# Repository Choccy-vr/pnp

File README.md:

# pnp
A manual precise pick and place machine for parts as small as 0402

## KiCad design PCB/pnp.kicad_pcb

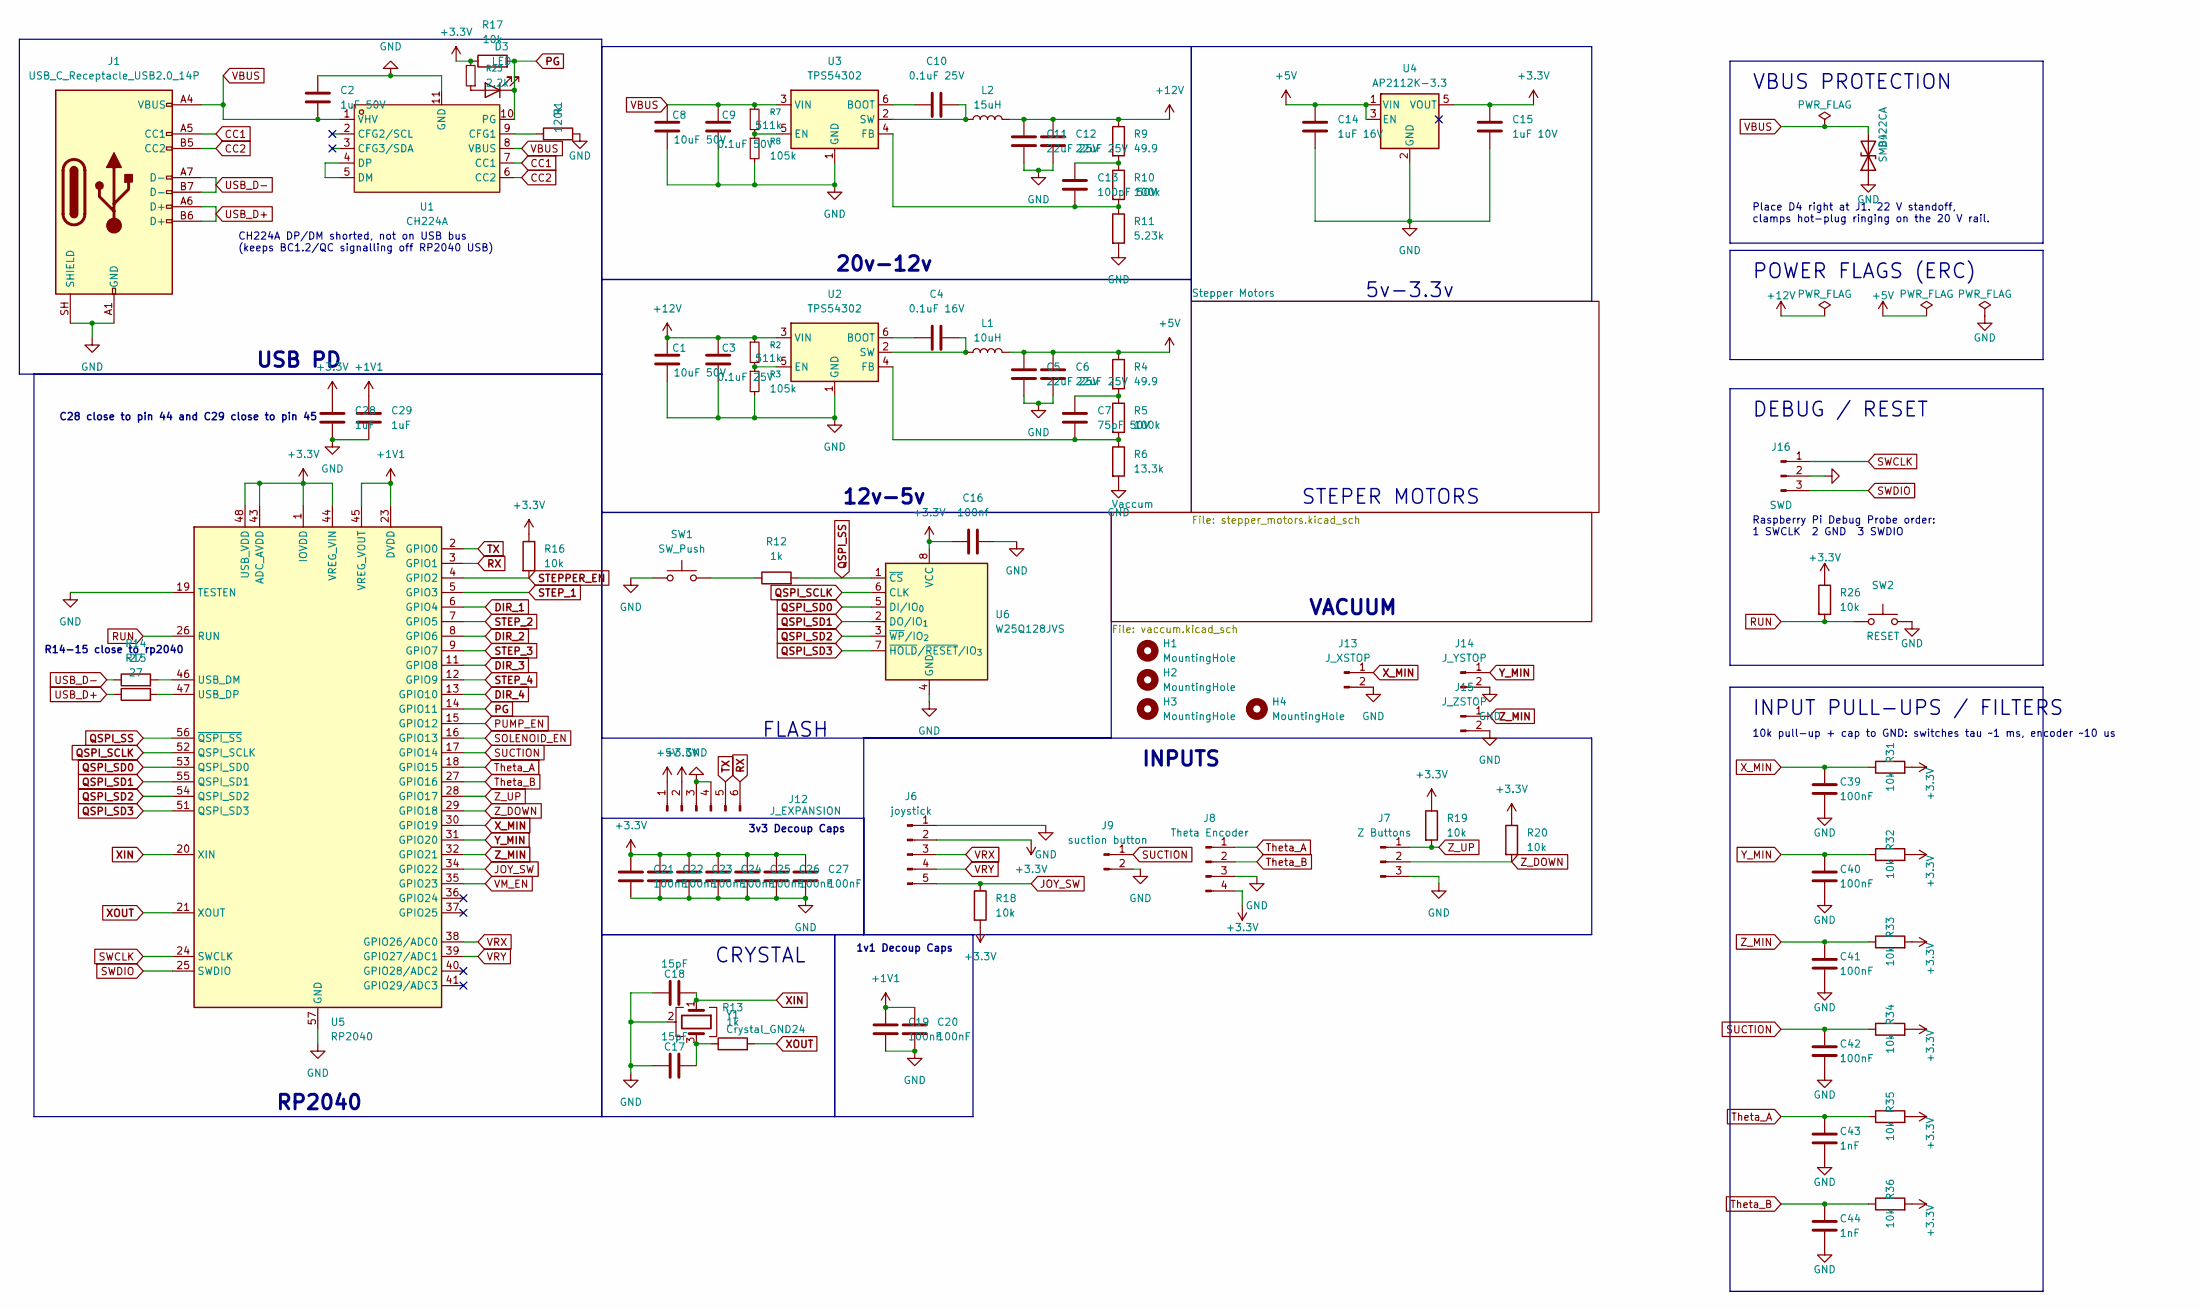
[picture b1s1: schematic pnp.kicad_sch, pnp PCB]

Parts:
C1, C8: 10uF 50V; C_1206_3216Metric; LCSC C13585
C2: 1uF 50V; C_0805_2012Metric; LCSC C28323
C3, C10: 0.1uF 25V; C_0402_1005Metric; LCSC C307331
C4: 0.1uF 16V; C_0402_1005Metric; LCSC C307331
C5, C6, C11, C12: 22uF 25V; C_1206_3216Metric; LCSC C12891
C7: 75pF 50V; C_0402_1005Metric; LCSC C107010
C9: 0.1uF 50V; C_0402_1005Metric; LCSC C307331
C13: 100pF 50V; C_0402_1005Metric; LCSC C1546
C14: 1uF 16V; C_0402_1005Metric; LCSC C52923
C15: 1uF 10V; C_0402_1005Metric; LCSC C52923
C16: 100nf; C_0402_1005Metric; LCSC C307331
C17, C18: 15pF; C_0402_1005Metric; LCSC C1548
C19, C20, C21, C22, C23, C24, C25, C26, C27, C39, C40, C41, C42: 100nF; C_0402_1005Metric; LCSC C307331
C28, C29: 1uF; C_0402_1005Metric; LCSC C52923
C43, C44: 1nF; C_0402_1005Metric; LCSC C1523
D3: LED; LED_0603_1608Metric
D4: SMBJ22CA; D_SMB; LCSC C19077577
H1, H2, H3, H4: MountingHole; MountingHole_3.2mm_M3
J1: USB_C_Receptacle_USB2.0_14P; USB_C_Receptacle_HRO_TYPE-C-31-M-12; LCSC C165948
J6: joystick; JST_XH_B5B-XH-A_1x05_P2.50mm_Vertical; LCSC C2908603
J7: Z Buttons; JST_XH_B3B-XH-A_1x03_P2.50mm_Vertical; LCSC C2908601
J8: Theta Encoder; JST_XH_B4B-XH-A_1x04_P2.50mm_Vertical; LCSC C2908602
J9: suction button; JST_XH_B2B-XH-A_1x02_P2.50mm_Vertical; LCSC C2908600
J12: J_EXPANSION; JST_XH_B6B-XH-A_1x06_P2.50mm_Vertical; LCSC C2908604
J13: J_XSTOP; JST_XH_B2B-XH-A_1x02_P2.50mm_Vertical; LCSC C2908600
J14: J_YSTOP; JST_XH_B2B-XH-A_1x02_P2.50mm_Vertical; LCSC C2908600
J15: J_ZSTOP; JST_XH_B2B-XH-A_1x02_P2.50mm_Vertical; LCSC C2908600
J16: SWD; JST_SH_SM03B-SRSS-TB_1x03-1MP_P1.00mm_Horizontal; LCSC C2845362
L1: 10uH; L_Bourns_SRN6045TA; LCSC C2046332
L2: 15uH; L_Bourns_SRN6045TA; LCSC C1330797
R1: 120k; R_0402_1005Metric; LCSC C25750
R2, R7: 511k; R_0402_1005Metric; LCSC C64042
R3, R8: 105k; R_0402_1005Metric; LCSC C2933067
R4, R9: 49.9; R_0402_1005Metric; LCSC C25120
R5, R10: 100k; R_0402_1005Metric; LCSC C25741
R6: 13.3k; R_0402_1005Metric; LCSC C274352
R11: 5.23k; R_0402_1005Metric; LCSC C2933105
R12, R13: 1k; R_0402_1005Metric; LCSC C11702
R14, R15: 27; R_0402_1005Metric; LCSC C2909343
R16, R17, R18, R19, R20, R26, R31, R32, R33, R34, R35, R36: 10k; R_0402_1005Metric; LCSC C25744
R23: 2.2k; R_0402_1005Metric; LCSC C25879
SW1: SW_Push; SW-SMD_L3.9-W3.0-P4.45; LCSC C720477
SW2: RESET; SW-SMD_L3.9-W3.0-P4.45; LCSC C720477
U1: CH224A; ESSOP-10_L4.9-W3.9-P1.0-LS6.0-TL-EP; MPN CH224A; LCSC Part C42459160
U2, U3: TPS54302; SOT-23-6; LCSC C311983
U4: AP2112K-3.3; SOT-23-5; LCSC C51118
U5: RP2040; QFN-56-1EP_7x7mm_P0.4mm_EP3.2x3.2mm; LCSC C2040
U6: W25Q128JVS; SOIC-8_5.3x5.3mm_P1.27mm; LCSC C97521
Y1: Crystal_GND24; Crystal_SMD_3225-4Pin_3.2x2.5mm

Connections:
+1V1: C19.1, C20.1, C29.1, U5.23 (DVDD), U5.45 (VREG_VOUT), U5.50 (DVDD)
+3.3V: C15.1, C16.1, C21.1, C22.1, C23.1, C24.1, C25.1, C26.1, C27.1, C28.1, J6.2, J8.4, J12.2, R16.1, R17.1, R18.2, R19.1, R20.1, R23.2, R26.1, R31.2, R32.2, R33.2, R34.2, R35.2, R36.2, U4.5 (VOUT), U5.1 (IOVDD), U5.10 (IOVDD), U5.22 (IOVDD), U5.33 (IOVDD), U5.42 (IOVDD), U5.43 (ADC_AVDD), U5.44 (VREG_VIN), U5.48 (USB_VDD), U5.49 (IOVDD), U6.8 (VCC); also elsewhere on the board
+5V: C5.1, C6.1, C14.1, J12.1, L1.2, R4.1, U4.1 (VIN), U4.3 (EN)
+12V: C1.1, C3.1, C11.1, C12.1, L2.2, R2.1, R9.1, U2.3 (VIN); also elsewhere on the board
CC1: J1.A5 (CC1), U1.7 (CC1)
CC2: J1.B5 (CC2), U1.6 (CC2)
DIR_1: U5.6 (GPIO4); also elsewhere on the board
DIR_2: U5.8 (GPIO6); also elsewhere on the board
DIR_3: U5.11 (GPIO8); also elsewhere on the board
DIR_4: U5.13 (GPIO10); also elsewhere on the board
GND: C1.2, C2.1, C3.2, C5.2, C6.2, C8.2, C9.2, C11.2, C12.2, C14.2, C15.2, C16.2, C17.1, C18.1, C19.2, C20.2, C21.2, C22.2, C23.2, C24.2, C25.2, C26.2, C27.2, C28.2, C29.2, C39.2, C40.2, C41.2, C42.2, C43.2, C44.2, D4.1 (A1), J1.A1 (GND), J1.A12 (GND), J1.B1 (GND), J1.B12 (GND), J1.SH (SHIELD), J6.1, J7.3, J8.3, J9.2, J12.3, J12.4, J13.2, J14.2, J15.2, J16.2, R1.2, R3.2, R6.2, R8.2, R11.2, SW1.1, SW2.2, U1.11 (GND), U2.1 (GND), U3.1 (GND), U4.2 (GND), U5.19 (TESTEN), U5.57 (GND), U6.4 (GND), Y1.2 (G), Y1.4 (G); also elsewhere on the board
JOY_SW: J6.5, R18.1, U5.34 (GPIO22)
unnamed: C7.1, R4.2, R5.1
unnamed: C13.1, R9.2, R10.1
unnamed: C17.2, R13.1, Y1.3
unnamed: D3.2 (A), R23.1
unnamed: R12.1, SW1.2
unnamed: R1.1, U1.9 (CFG1)
unnamed: U1.4 (DP), U1.5 (DM)
unnamed: C4.1, U2.6 (BOOT)
unnamed: R2.2, R3.1, U2.5 (EN)
unnamed: C7.2, R5.2, R6.1, U2.4 (FB)
unnamed: C4.2, L1.1, U2.2 (SW)
unnamed: C10.1, U3.6 (BOOT)
unnamed: R7.2, R8.1, U3.5 (EN)
unnamed: C13.2, R10.2, R11.1, U3.4 (FB)
unnamed: C10.2, L2.1, U3.2 (SW)
unnamed: R14.2, U5.46 (USB_DM)
unnamed: R15.2, U5.47 (USB_DP)
PG: D3.1 (K), R17.2, U1.10 (PG), U5.14 (GPIO11)
PUMP_EN: U5.15 (GPIO12); also elsewhere on the board
QSPI_SCLK: U5.52 (QSPI_SCLK), U6.6 (CLK)
QSPI_SD0: U5.53 (QSPI_SD0), U6.5 (DI/IO_{0})
QSPI_SD1: U5.55 (QSPI_SD1), U6.2 (DO/IO_{1})
QSPI_SD2: U5.54 (QSPI_SD2), U6.3 (~WP/IO_{2})
QSPI_SD3: U5.51 (QSPI_SD3), U6.7 (~HOLD/~RESET/IO_{3})
QSPI_SS: R12.2, U5.56 (~QSPI_SS), U6.1 (~CS)
RUN: R26.2, SW2.1, U5.26 (RUN)
RX: J12.6, U5.3 (GPIO1)
SOLENOID_EN: U5.16 (GPIO13); also elsewhere on the board
STEPPER_EN: R16.2, U5.4 (GPIO2); also elsewhere on the board
STEP_1: U5.5 (GPIO3); also elsewhere on the board
STEP_2: U5.7 (GPIO5); also elsewhere on the board
STEP_3: U5.9 (GPIO7); also elsewhere on the board
STEP_4: U5.12 (GPIO9); also elsewhere on the board
SUCTION: C42.1, J9.1, R34.1, U5.17 (GPIO14)
SWCLK: J16.1, U5.24 (SWCLK)
SWDIO: J16.3, U5.25 (SWDIO)
TX: J12.5, U5.2 (GPIO0)
Theta_A: C43.1, J8.1, R35.1, U5.18 (GPIO15)
Theta_B: C44.1, J8.2, R36.1, U5.27 (GPIO16)
USB_D+: J1.A6 (D+), J1.B6 (D+), R15.1
USB_D-: J1.A7 (D-), J1.B7 (D-), R14.1
VBUS: C2.2, C8.1, C9.1, D4.2 (A2), J1.A4 (VBUS), J1.A9 (VBUS), J1.B4 (VBUS), J1.B9 (VBUS), R7.1, U1.1 (VHV), U1.8 (VBUS), U3.3 (VIN); also elsewhere on the board
VM_EN: U5.35 (GPIO23); also elsewhere on the board
VRX: J6.3, U5.38 (GPIO26/ADC0)
VRY: J6.4, U5.39 (GPIO27/ADC1)
XIN: C18.2, U5.20 (XIN), Y1.1
XOUT: R13.2, U5.21 (XOUT)
X_MIN: C39.1, J13.1, R31.1, U5.30 (GPIO19)
Y_MIN: C40.1, J14.1, R32.1, U5.31 (GPIO20)
Z_DOWN: J7.2, R20.2, U5.29 (GPIO18)
Z_MIN: C41.1, J15.1, R33.1, U5.32 (GPIO21)
Z_UP: J7.1, R19.2, U5.28 (GPIO17)

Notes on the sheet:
Raspberry Pi Debug Probe order: 1 SWCLK 2 GND 3 SWDIO
DEBUG / RESET
RP2040
STEPER MOTORS
C28 close to pin 44 and C29 close to pin 45
USB PD
R14-15 close to rp2040
FLASH
1v1 Decoup Caps
Place D4 right at J1. 22 V standoff, clamps hot-plug ringing on the 20 V rail.
VBUS PROTECTION
5v-3.3v
12v-5v
VACUUM
INPUT PULL-UPS / FILTERS
10k pull-up + cap to GND: switches tau ~1 ms, encoder ~10 us
POWER FLAGS (ERC)
INPUTS
20v-12v
CRYSTAL
3v3 Decoup Caps
CH224A DP/DM shorted, not on USB bus (keeps BC1.2/QC signalling off RP2040 USB)

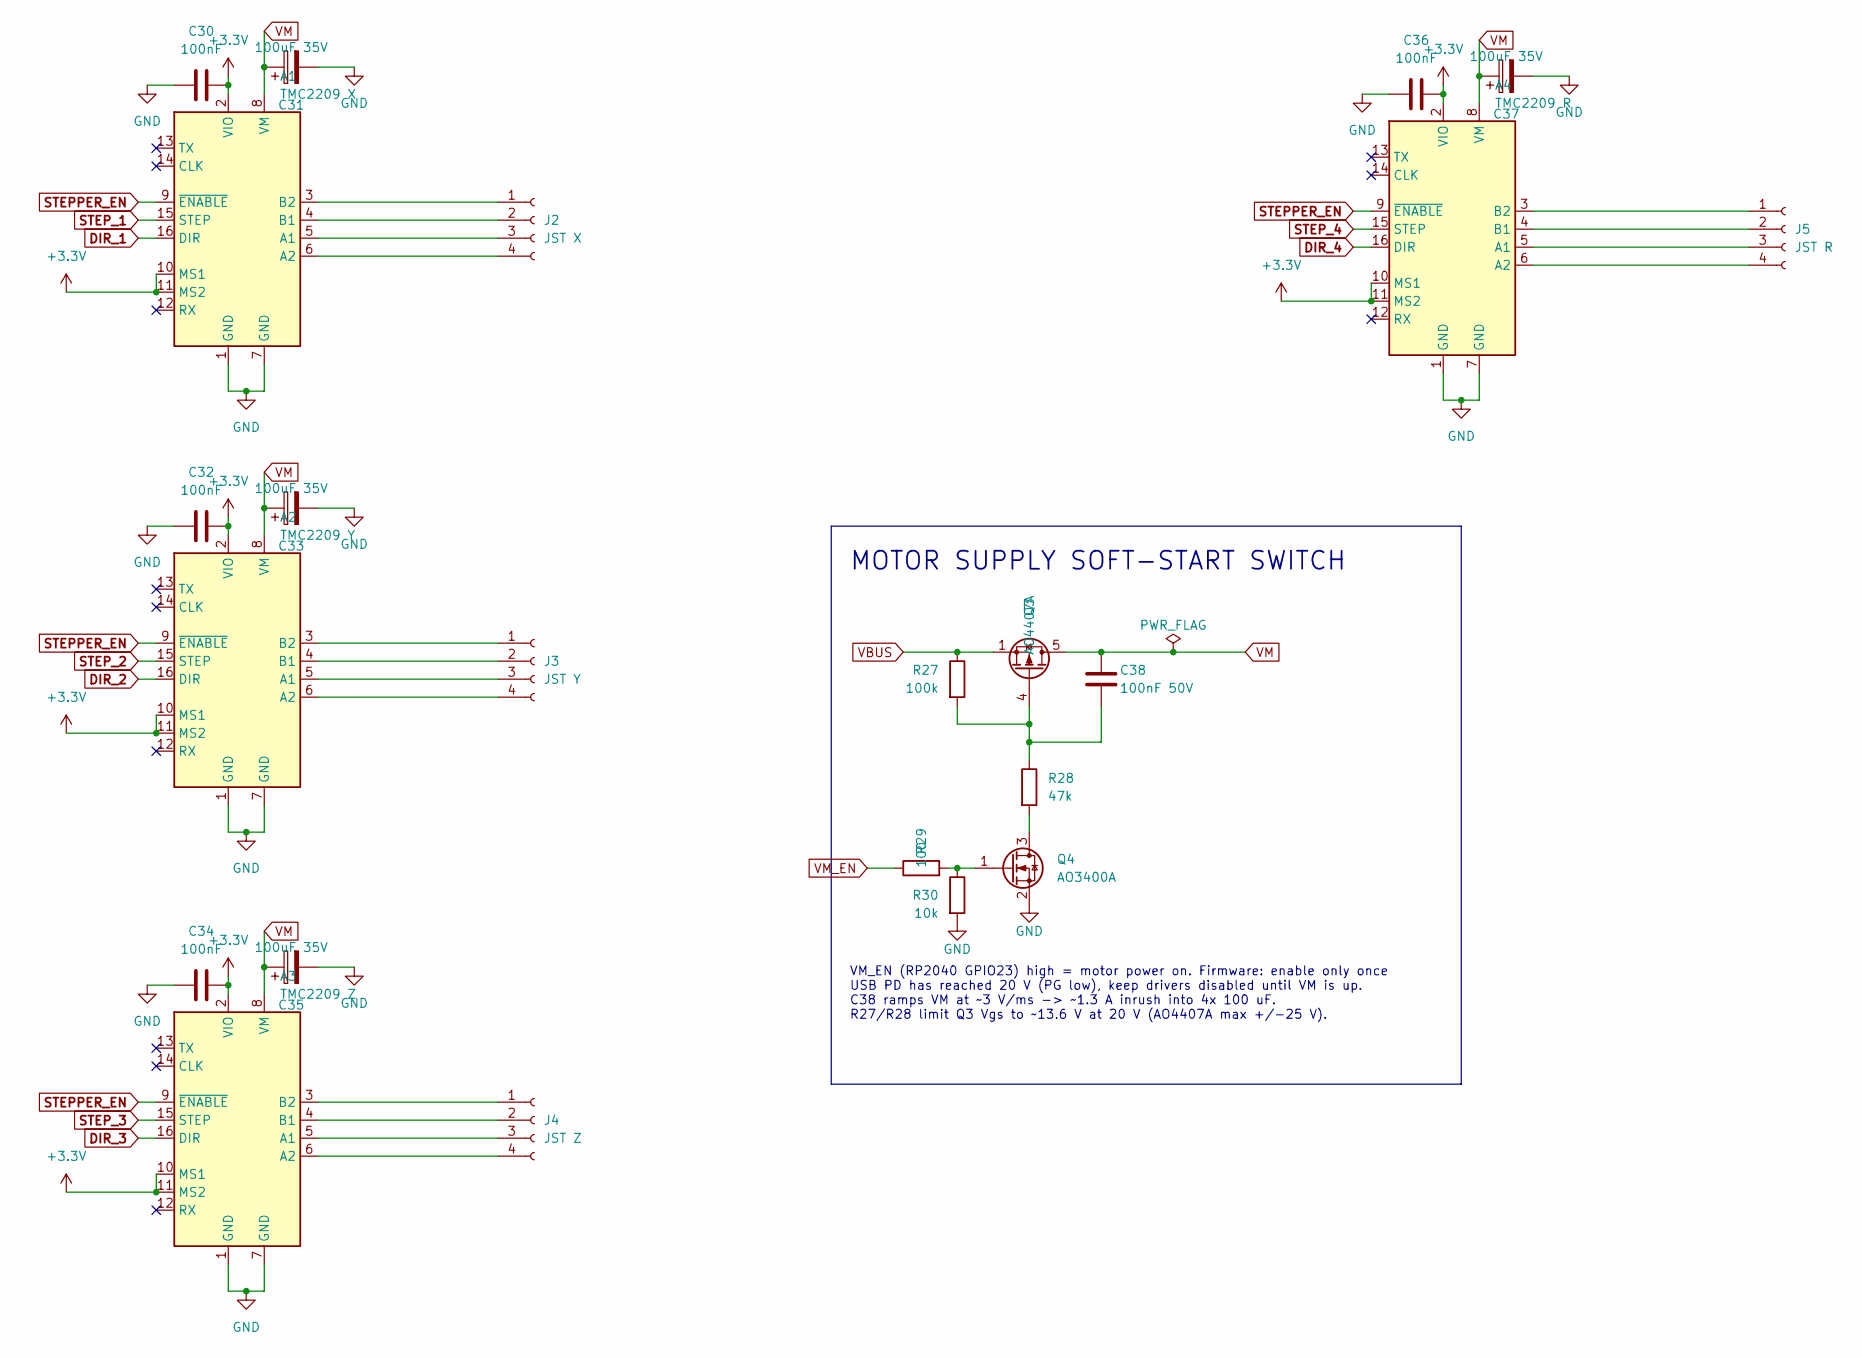
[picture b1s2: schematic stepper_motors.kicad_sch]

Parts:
A1: TMC2209 X; Pololu_Breakout-16_15.2x20.3mm
A2: TMC2209 Y; Pololu_Breakout-16_15.2x20.3mm
A3: TMC2209 Z; Pololu_Breakout-16_15.2x20.3mm
A4: TMC2209 R; Pololu_Breakout-16_15.2x20.3mm
C30, C32, C34, C36: 100nF; C_0402_1005Metric; LCSC C307331
C31, C33, C35, C37: 100uF 35V; CP_Radial_D6.3mm_P2.50mm; LCSC C106694
C38: 100nF 50V; C_0402_1005Metric; LCSC C307331
J2: JST X; JST_XH_B4B-XH-A_1x04_P2.50mm_Vertical; LCSC C2908602
J3: JST Y; JST_XH_B4B-XH-A_1x04_P2.50mm_Vertical; LCSC C2908602
J4: JST Z; JST_XH_B4B-XH-A_1x04_P2.50mm_Vertical; LCSC C2908602
J5: JST R; JST_XH_B4B-XH-A_1x04_P2.50mm_Vertical; LCSC C2908602
Q3: AO4407A; SOIC-8_3.9x4.9mm_P1.27mm; LCSC C16072
Q4: AO3400A; SOT-23; LCSC C20917
R27: 100k; R_0402_1005Metric; LCSC C25741
R28: 47k; R_0402_1005Metric; LCSC C25792
R29: 100; R_0402_1005Metric; LCSC C25076
R30: 10k; R_0402_1005Metric; LCSC C25744

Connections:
+3.3V: A1.2 (VIO), A1.10 (MS1), A1.11 (MS2), A2.2 (VIO), A2.10 (MS1), A2.11 (MS2), A3.2 (VIO), A3.10 (MS1), A3.11 (MS2), A4.2 (VIO), A4.10 (MS1), A4.11 (MS2), C30.1, C32.1, C34.1, C36.1; also elsewhere on the board
DIR_1: A1.16 (DIR); also elsewhere on the board
DIR_2: A2.16 (DIR); also elsewhere on the board
DIR_3: A3.16 (DIR); also elsewhere on the board
DIR_4: A4.16 (DIR); also elsewhere on the board
GND: A1.1 (GND), A1.7 (GND), A2.1 (GND), A2.7 (GND), A3.1 (GND), A3.7 (GND), A4.1 (GND), A4.7 (GND), C30.2, C31.2, C32.2, C33.2, C34.2, C35.2, C36.2, C37.2, Q4.2 (S), R30.2; also elsewhere on the board
unnamed: A1.5 (A1), J2.3
unnamed: A1.6 (A2), J2.4
unnamed: A1.4 (B1), J2.2
unnamed: A1.3 (B2), J2.1
unnamed: A2.5 (A1), J3.3
unnamed: A2.6 (A2), J3.4
unnamed: A2.4 (B1), J3.2
unnamed: A2.3 (B2), J3.1
unnamed: A3.5 (A1), J4.3
unnamed: A3.6 (A2), J4.4
unnamed: A3.4 (B1), J4.2
unnamed: A3.3 (B2), J4.1
unnamed: A4.5 (A1), J5.3
unnamed: A4.6 (A2), J5.4
unnamed: A4.4 (B1), J5.2
unnamed: A4.3 (B2), J5.1
unnamed: C38.2, Q3.4 (G), R27.2, R28.1
unnamed: Q4.3 (D), R28.2
unnamed: Q4.1 (G), R29.2, R30.1
STEPPER_EN: A1.9 (~ENABLE), A2.9 (~ENABLE), A3.9 (~ENABLE), A4.9 (~ENABLE); also elsewhere on the board
STEP_1: A1.15 (STEP); also elsewhere on the board
STEP_2: A2.15 (STEP); also elsewhere on the board
STEP_3: A3.15 (STEP); also elsewhere on the board
STEP_4: A4.15 (STEP); also elsewhere on the board
VBUS: Q3.1 (S), Q3.2 (S), Q3.3 (S), R27.1; also elsewhere on the board
VM: A1.8 (VM), A2.8 (VM), A3.8 (VM), A4.8 (VM), C31.1, C33.1, C35.1, C37.1, C38.1, Q3.5 (D), Q3.6 (D), Q3.7 (D), Q3.8 (D)
VM_EN: R29.1; also elsewhere on the board

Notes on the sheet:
MOTOR SUPPLY SOFT-START SWITCH
VM_EN (RP2040 GPIO23) high = motor power on. Firmware: enable only once USB PD has reached 20 V (PG low), keep drivers disabled until VM is up. C38 ramps VM at ~3 V/ms -> ~1.3 A inrush into 4x 100 uF. R27/R28 limit Q3 Vgs to ~13.6 V at 20 V (AO4407A max +/-25 V).

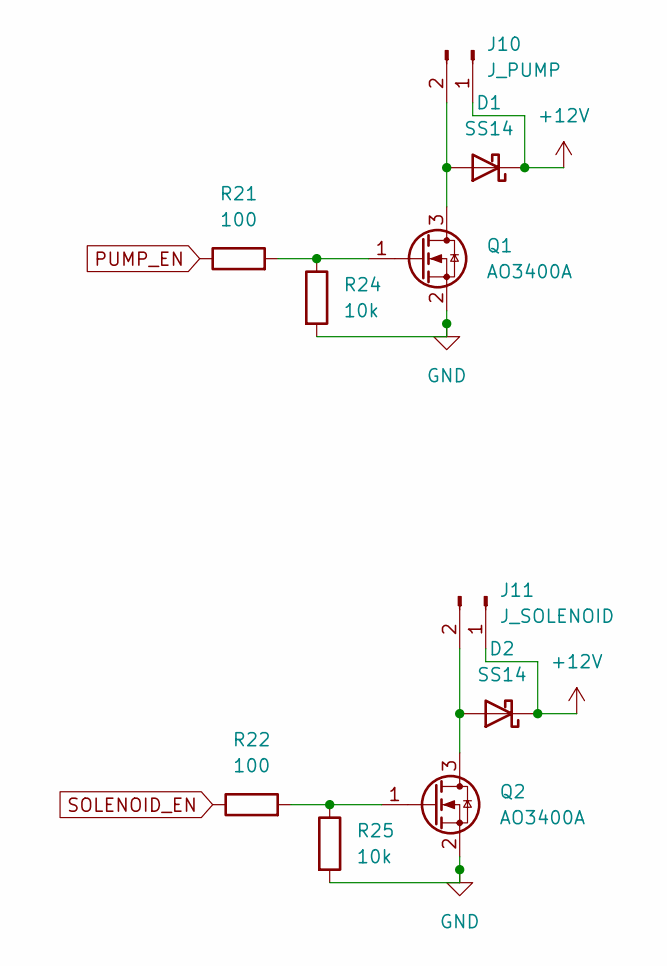
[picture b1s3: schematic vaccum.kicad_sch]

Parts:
D1, D2: SS14; D_SMA; LCSC C2480
J10: J_PUMP; JST_XH_B2B-XH-A_1x02_P2.50mm_Vertical; LCSC C2908600
J11: J_SOLENOID; JST_XH_B2B-XH-A_1x02_P2.50mm_Vertical; LCSC C2908600
Q1, Q2: AO3400A; SOT-23; LCSC C20917
R21, R22: 100; R_0402_1005Metric; LCSC C25076
R24, R25: 10k; R_0402_1005Metric; LCSC C25744

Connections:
+12V: D1.1 (K), D2.1 (K), J10.1, J11.1; also elsewhere on the board
GND: Q1.2 (S), Q2.2 (S), R24.2, R25.2; also elsewhere on the board
unnamed: D1.2 (A), J10.2, Q1.3 (D)
unnamed: D2.2 (A), J11.2, Q2.3 (D)
unnamed: Q1.1 (G), R21.2, R24.1
unnamed: Q2.1 (G), R22.2, R25.1
PUMP_EN: R21.1; also elsewhere on the board
SOLENOID_EN: R22.1; also elsewhere on the board

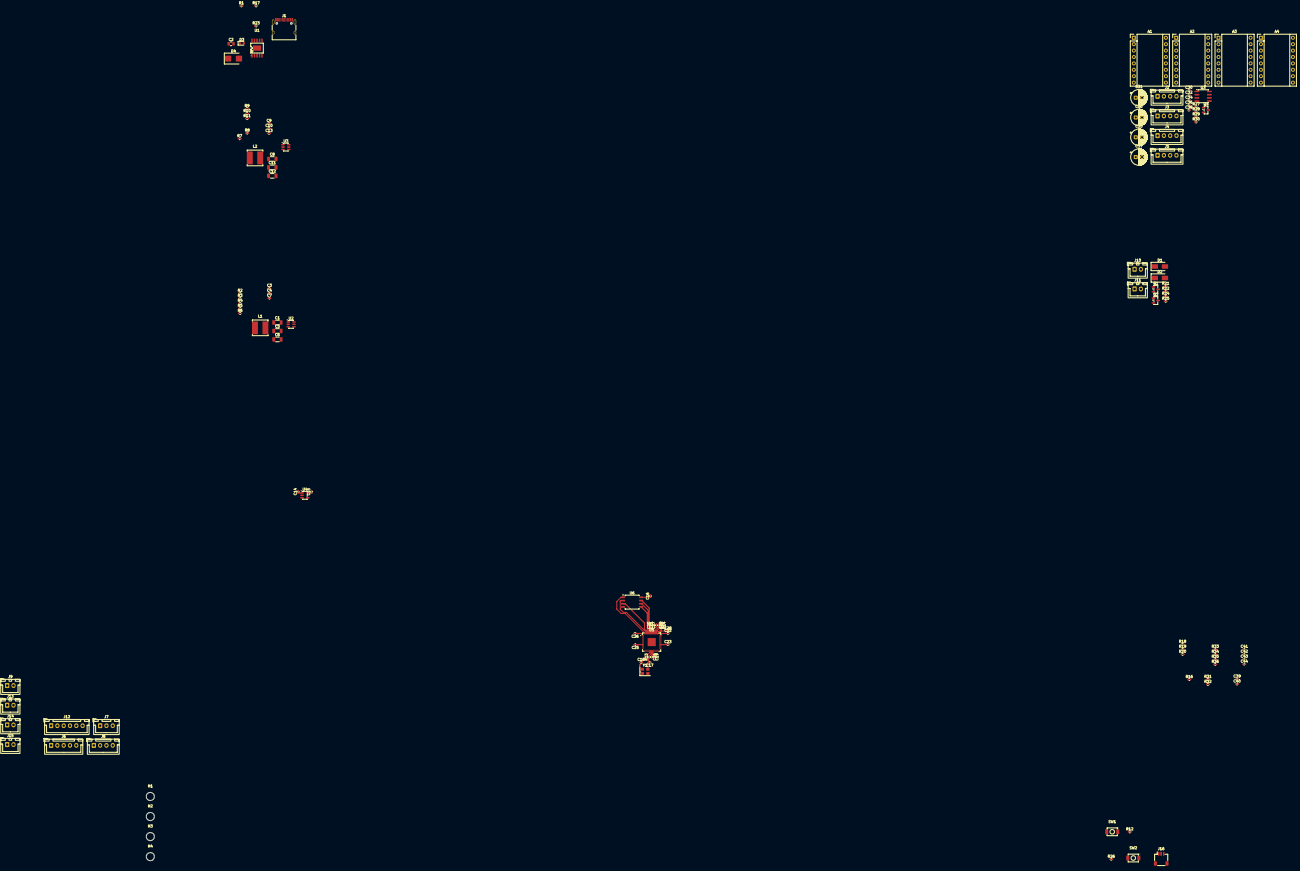
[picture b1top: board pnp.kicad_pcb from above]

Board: 4 copper layers, 123 parts (0 on the bottom side), 88 nets.
